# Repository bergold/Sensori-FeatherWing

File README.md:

# Sensorimotor FeatherWing

This FeatherWing lets you connect your Feather to a RS-485 bus. It also provides various ways of providing power to your RS-485 bus system, as well as the ability to back-power the Feather from the bus.

The bus connector is compatible to the Sensorimotor system. (It's a 4-pin Molex Mini-SPOX)

**Warning**: Usually Feathers don’t have a reverse USB back-feed protection. You might damage your USB port when the „Power>Feather“ switch is on. So, always turn it off before connecting a USB cable to the Feather.

→ [KiCAD Files](https://github.com/bergold/Sensori-FeatherWing)

## Schematic

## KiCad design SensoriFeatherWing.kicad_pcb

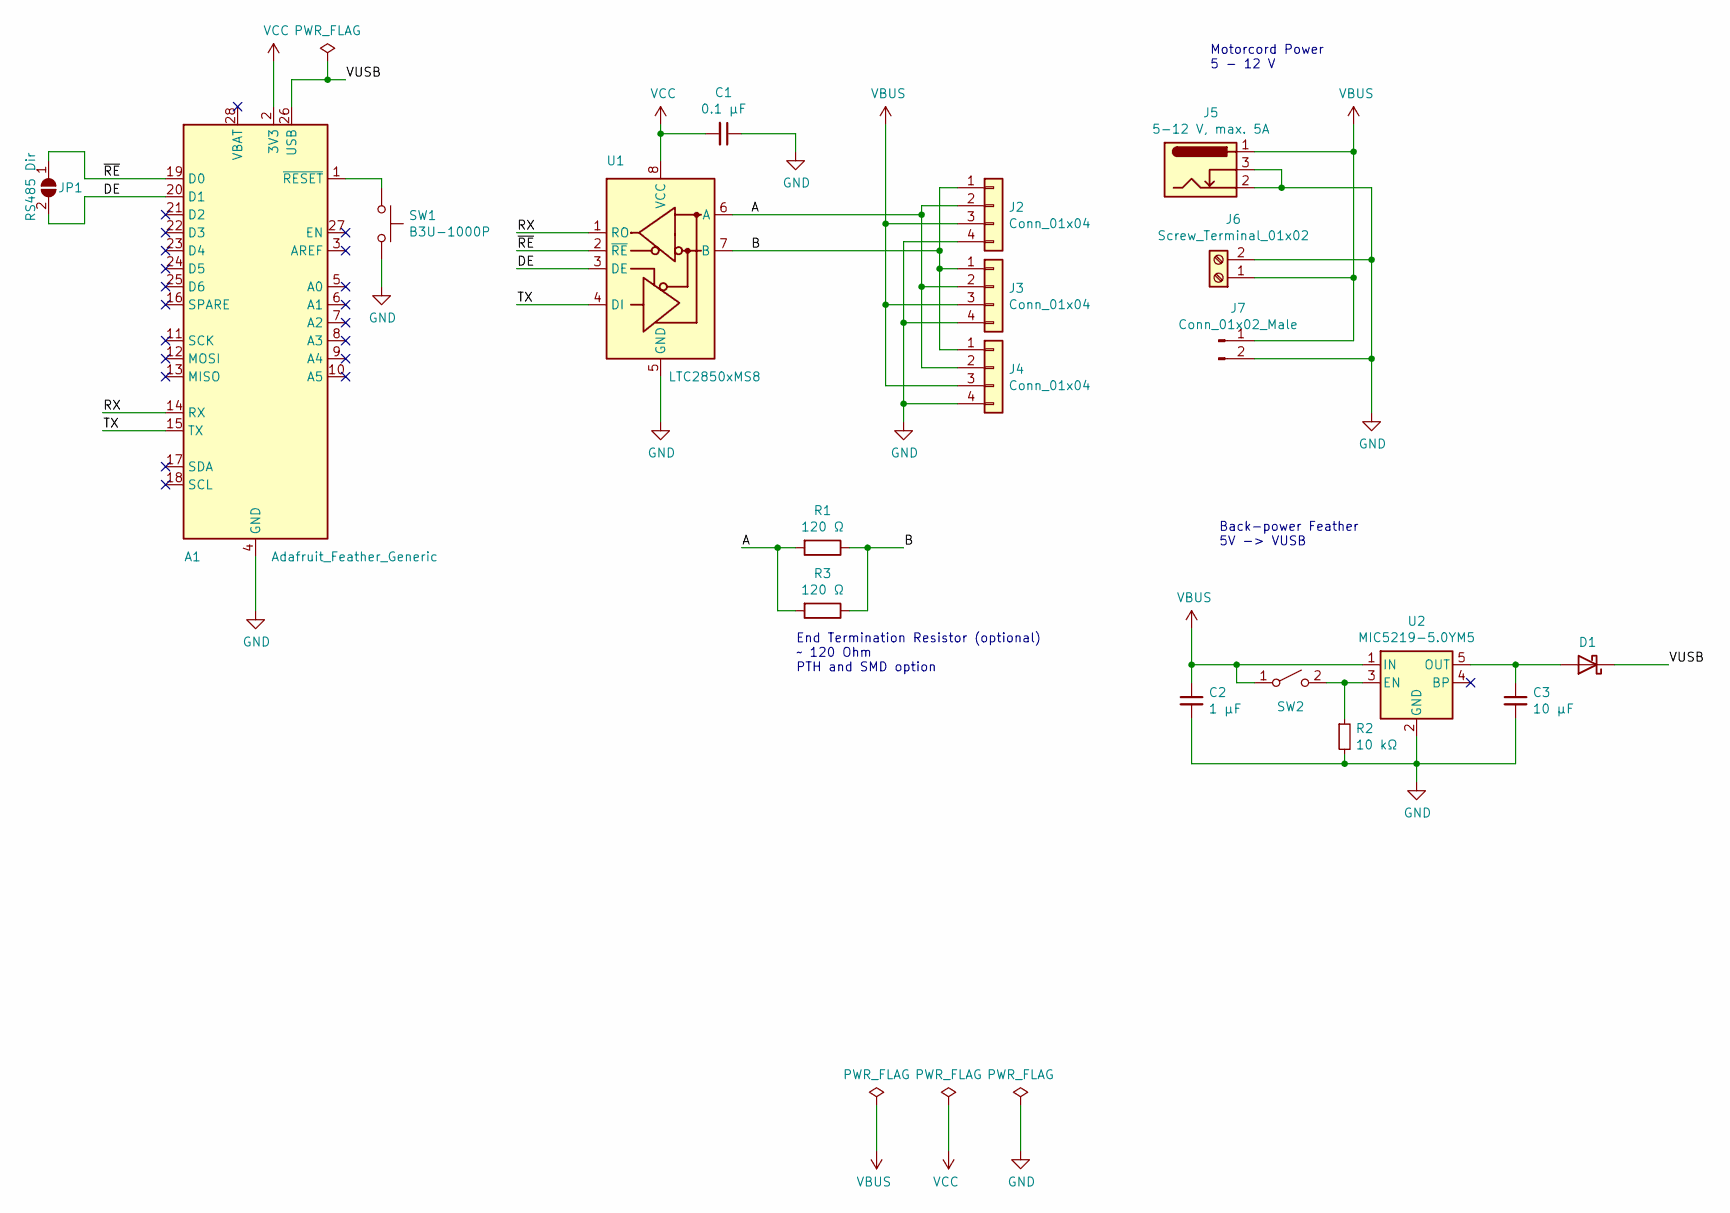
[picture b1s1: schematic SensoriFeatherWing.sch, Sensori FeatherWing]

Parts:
A1: Adafruit_Feather_Generic; Adafruit_Feather_WithMountingHoles
C1: 0.1 µF; C_0805_2012Metric_Pad1.18x1.45mm_HandSolder
C2: 1 µF; C_0805_2012Metric_Pad1.18x1.45mm_HandSolder
C3: 10 µF; C_0805_2012Metric_Pad1.18x1.45mm_HandSolder
D1: D_Schottky; D_SOD-323_HandSoldering
J2, J3, J4: Conn_01x04; Molex_SPOX_5267-04A_1x04_P2.50mm_Vertical
J5: 5-12 V, max. 5A; BarrelJack_Horizontal
J6: Screw_Terminal_01x02; TerminalBlock_4Ucon_1x02_P3.50mm_Horizontal
J7: Conn_01x02_Male; PinHeader_1x02_P2.54mm_Vertical
JP1: RS485 Dir; SolderJumper-2_P1.3mm_Open_TrianglePad1.0x1.5mm
R1: 120 Ω; R_Axial_DIN0204_L3.6mm_D1.6mm_P5.08mm_Horizontal
R2: 10 kΩ; R_0603_1608Metric_Pad0.98x0.95mm_HandSolder
R3: 120 Ω; R_0805_2012Metric_Pad1.20x1.40mm_HandSolder
SW1: B3U-1000P; SW_SPST_B3U-1000P
SW2: SW_SPST; SW_DS04-254-1L-01BK
U1: LTC2850xMS8; MSOP-8_3x3mm_P0.65mm
U2: MIC5219-5.0YM5; SOT-23-5

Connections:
/A: J2.2, J3.2, J4.2, R1.2, R3.2, U1.6 (A)
/B: J2.1, J3.1, J4.1, R1.1, R3.1, U1.7 (B)
/DE: A1.20 (D1), JP1.2 (B), U1.3 (DE)
/RX: A1.14 (RX), U1.1 (RO)
/TX: A1.15 (TX), U1.4 (DI)
/VUSB: A1.26 (USB), D1.1 (K)
/~RE: A1.19 (D0), JP1.1 (A), U1.2 (~RE)
GND: A1.4 (GND), C1.1, C2.2, C3.2, J2.4, J3.4, J4.4, J5.2, J5.3, J6.2, J7.2, R2.2, SW1.2, U1.5 (GND), U2.2 (GND)
unnamed: A1.1 (~RESET), SW1.1
unnamed: C3.1, D1.2 (A), U2.5 (OUT)
unnamed: R2.1, SW2.2 (B), U2.3 (EN)
VBUS: C2.1, J2.3, J3.3, J4.3, J5.1, J6.1, J7.1, SW2.1 (A), U2.1 (IN)
VCC: A1.2 (3V3), C1.2, U1.8 (VCC)

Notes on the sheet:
End Termination Resistor (optional) ~~ 120 Ohm PTH and SMD option
Motorcord Power 5 - 12 V
Back-power Feather 5V -> VUSB

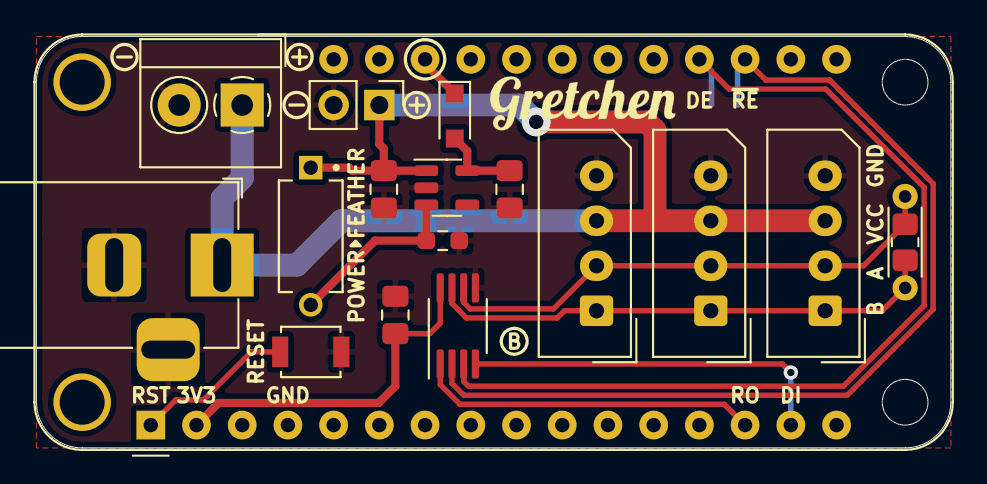
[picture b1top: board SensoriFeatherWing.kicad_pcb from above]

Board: 2 copper layers, 50.8 x 22.9 mm, 19 parts (1 on the bottom side), 13 nets.

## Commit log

2020-11-17 updated silkscreen
2020-11-23 Exported artifacts
2020-11-25 Update pcb
2020-11-25 add README
2020-12-08 digikey part numbers
2020-12-08 revision code on front silk
2020-12-08 warning on USB back-feeding
